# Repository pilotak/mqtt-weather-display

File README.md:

# MQTT weather display

Simple weather and time display, ready to be controlled from MQTT, based on ESP8266, ILI9341 and DS3231. Icon names are based on clientraw format weather station.

**Custom component from clientraw weather station for HomeAssistant can be found [here](https://github.com/pilotak/homeassistant-clientraw)**

HomeAssistant config:

```yaml
# automations.yaml
- alias: Forecast change
  initial_state: True
  trigger:
    platform: state
    entity_id: sensor.clientraw_symbol
  condition:
    condition: template
    value_template: '{{ trigger.from_state.state != trigger.to_state.state }}'
  action:
    service: mqtt.publish
    data_template:
      topic: "mqtt-weather-display/forecast"
      qos: 1
      retain: true
      payload: >
        {%- set symbol = states.sensor.clientraw_symbol.state -%}
        {%- if symbol is not none and symbol != "unavailable" -%}
          {{ symbol }}
        {%- endif -%}

- alias: Outside temp change
  initial_state: True
  trigger:
    platform: state
    entity_id: sensor.clientraw_temperature
  condition:
    condition: template
    value_template: '{{ trigger.from_state.state != trigger.to_state.state }}'
  action:
    service: mqtt.publish
    data_template:
      topic: "mqtt-weather-display/out-temp"
      qos: 1
      retain: true
      payload: >
        {%- set out_temp = states.sensor.clientraw_temperature.state -%}
        {%- if out_temp is not none and out_temp != "unavailable" -%}
          {{ out_temp }}
        {%- endif -%}

- alias: Inside temp change
  initial_state: True
  trigger:
    platform: state
    entity_id: sensor.myslipotemp_1_0
  condition:
    condition: template
    value_template: '{{ trigger.from_state.state != trigger.to_state.state }}'
  action:
    service: mqtt.publish
    data_template:
      topic: "mqtt-weather-display/in-temp"
      qos: 1
      retain: true
      payload: >
        {%- set in_temp = states.sensor.myslipotemp_1_0.state -%}
        {%- if in_temp is not none and in_temp != "unavailable" -%}
          {{ in_temp }}
        {%- endif -%}

- alias: Outside feel temp change
  initial_state: True
  trigger:
    platform: state
    entity_id: sensor.clientraw_humidex
  condition:
    condition: template
    value_template: '{{ trigger.from_state.state != trigger.to_state.state }}'
  action:
    service: mqtt.publish
    data_template:
      topic: "mqtt-weather-display/out-temp-feel"
      qos: 1
      retain: true
      payload: >
        {%- set out_temp_feel = states.sensor.clientraw_humidex.state -%}
        {%- if out_temp_feel is not none and out_temp_feel != "unavailable" -%}
          {{ out_temp_feel }}
        {%- endif -%}
```

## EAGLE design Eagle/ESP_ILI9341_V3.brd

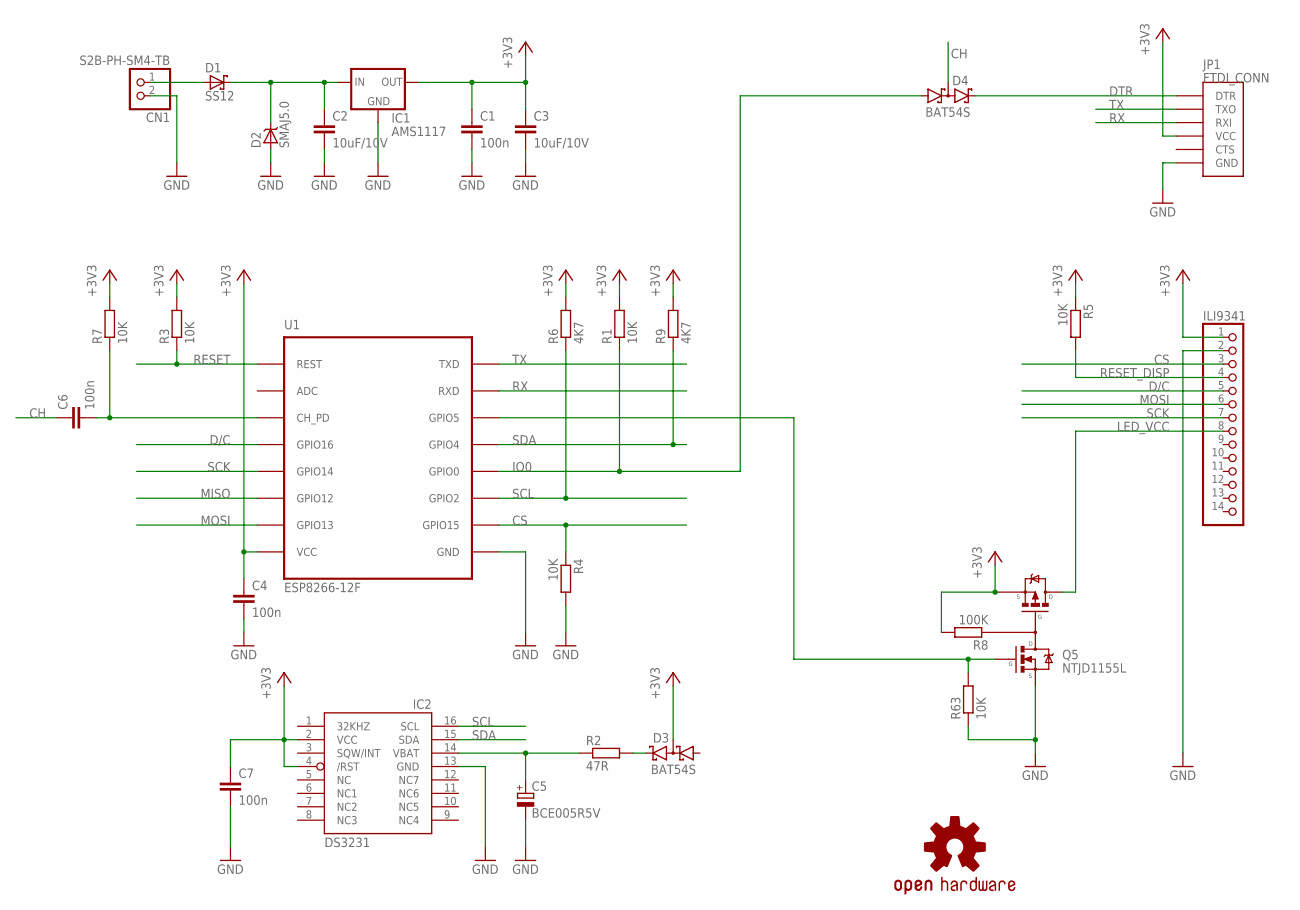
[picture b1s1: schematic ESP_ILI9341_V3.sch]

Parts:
C1, C4, C6, C7: 100n; C0805
C2, C3: 10uF/10V; C0805
C5: BCE005R5V; BCE
CN1: S2B-PH-SM4-TB; JST-PH-2-SMT-RA
D1: SS12; DO214AC
D2: SMAJ5.0; DO214AC
D3, D4: BAT54S; SOT23
IC1: AMS1117; SOT223
IC2: DS3231/SO; SO16W
ILI9341: PINHD-1X14; 1X14
JP1: FTDI_CONN; FTDI
LOGO1: OSHW-LOGOM-COPPER; OSHW-LOGO-M_COPPER
Q5: NTJD1155L; SOT363
R1, R3, R4, R5, R7, R63: 10K; R0805
R2: 47R; R1206
R6, R9: 4K7; R0805
R8: 100K; R0805
U1: ESP8266-12F; ESP-12

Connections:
+3V3: C1.1, C3.1, C4.1, C7.1, D3.3 (C1A2), IC1.2 (OUT), IC1.4 (OUT), IC2.2 (VCC), IC2.4 (/RST), ILI9341.1, JP1.P$4 (VCC), Q5.4 (S2), R1.2, R3.2, R5.1, R6.2, R7.2, R8.2, R9.2, U1.VCC
CH: C6.1, D4.3 (C1A2)
CS: ILI9341.3, R4.1, U1.GPIO15
D/C: ILI9341.5, U1.GPIO16
DTR: D4.2 (C2), JP1.P$1 (DTR)
GND: C1.2, C2.2, C3.2, C4.2, C5.-, C7.2, CN1.2 (1), D2.A, IC1.1 (GND), IC2.13 (GND), ILI9341.2, JP1.P$6 (GND), Q5.1 (S1), R4.2, R63.1, U1.GND
IO0: D4.1 (A1), R1.1, U1.GPIO0
LED_VCC: ILI9341.8, Q5.2 (D2), Q5.3 (D2)
MISO: U1.GPIO12
MOSI: ILI9341.6, U1.GPIO13
unnamed: D3.2 (C2), R2.2
unnamed: CN1.1 (2), D1.A
unnamed: C2.1, D1.C, D2.C, IC1.3 (IN)
unnamed: C6.2, R7.1, U1.CH_PD
unnamed: C5.+, IC2.14 (VBAT), R2.1
unnamed: Q5.6 (D1/G2), R8.1
unnamed: Q5.5 (G1), R63.2, U1.GPIO5
RESET: R3.1, U1.REST
RESET_DISP: ILI9341.4, R5.2
RX: JP1.P$3 (RXI), U1.RXD
SCK: ILI9341.7, U1.GPIO14
SCL: IC2.16 (SCL), R6.1, U1.GPIO2
SDA: IC2.15 (SDA), R9.1, U1.GPIO4
TX: JP1.P$2 (TXO), U1.TXD

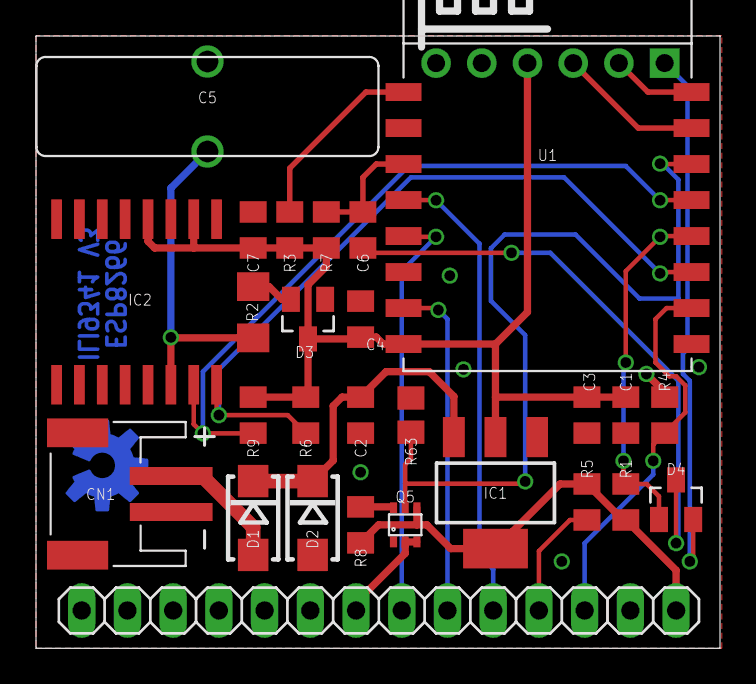
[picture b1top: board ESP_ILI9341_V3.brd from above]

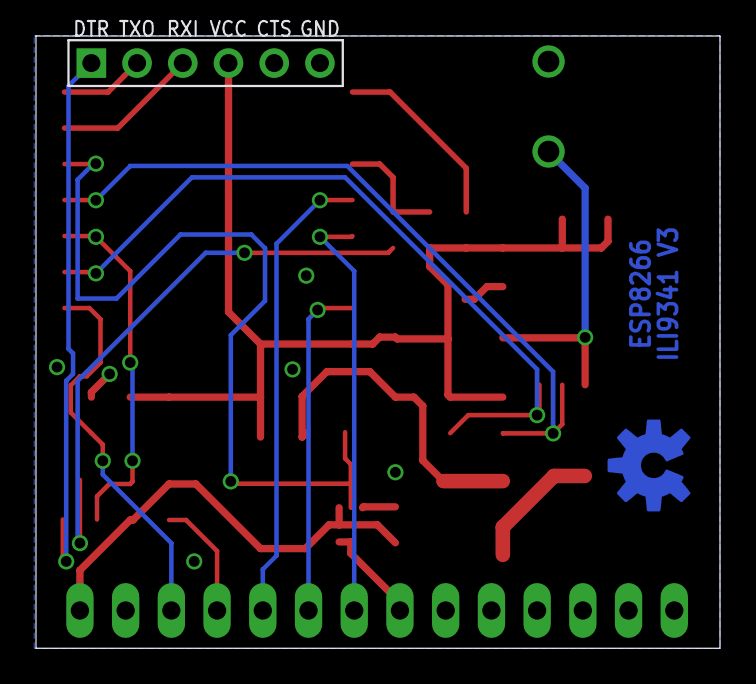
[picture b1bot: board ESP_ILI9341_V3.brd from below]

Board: 2 copper layers, 38.0 x 34.0 mm, 29 parts (2 on the bottom side), 23 nets.

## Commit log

2017-04-04 first version
2017-04-06 night mode
2017-05-17 pin update
2017-07-02 readme
2018-01-01 Hardware RTC added
2018-03-07 licence change
2018-05-23 moved to platform.io
2019-07-05 reworked to ASYNC
2019-07-18 bug fix
2019-07-18 PIO 4
2019-08-06 atoi & atof only from buffer with exact length
2019-09-06 travis
2019-09-06 test
2019-09-06 case test2
2019-09-06 case sensitive
2019-09-07 eagle files
2019-09-07 automation update
2020-02-01 bug fix MQTT lib
2020-02-01 use RTC as default time provider + NTP resync
2020-02-01 wifi manager update
2020-08-16 folder restructure
2020-08-16 moved from Travis to GithubCI
2020-08-16 remove travis config
2020-08-16 move schematic under hw
2020-08-16 CI update
2020-09-24 Ci split build & release
2020-09-24 update deps to include owner

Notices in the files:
parts and their libraries:
SparkFun-Aesthetics: Licensing: Creative Commons ShareAlike 4.0 International - https://creativecommons.org/licenses/by-sa/4.0
